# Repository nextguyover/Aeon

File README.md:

# Aeon

Aeon is a solar-powered colour e-ink photo frame designed around the [7.3inch Spectra 6](https://www.waveshare.com/7.3inch-e-paper-hat-e.htm) e-ink display. Powered using energy harvesting, Aeon achieves indefinite operation when placed in a bright indoor environment.

This repository contains the following design files for Aeon. 

- [Firmware](firmware)
- [Image Conversion Script](image_conversion)
- [Schematic and PCB Design](schematic_and_PCB)

See the the [blogpost](https://insertnewline.com/blog/aeon/) for a full write-up and additional file downloads.

Current Aeon version is v2.0, available on the [main branch](https://github.com/nextguyover/Aeon/tree/main). See older versions below:
- [v1.4](https://github.com/nextguyover/Aeon/tree/v1.4) - Using discontinued [7.3inch ACeP](https://www.waveshare.com/7.3inch-e-paper-hat-f.htm) e-ink display

## Firmware

The `/firmware` directory contains the firmware for the STM32 microcontroller.

### Flashing

Before flashing the firmware, the option bytes of the STM32 must be set. Using STM32CubeProgrammer, uncheck nSWBOOT0. The option byte options should look like this:

Next, flashing the firmware can be done using the STM32CubeIDE. Your STLink programmer should be connected to the programming pins on the PCB.

### Debugging

The firmware includes several debugging features. 

Any `printf` statements will be outputted to SWO, which can be read using STLink. Additionally, if debug mode is active, any logged data will be stored in an array, and written to the SD card just before going back to sleep. This debug mode is enabled by pressing and **holding** the refresh button to wake the device. The status LED will **flash rapidly** to indicate debug mode is active. Alternatively, the `DEBUG_MODE_FORCE_EN` flag in `main.h` forces debug mode to be enabled. This should be disabled during normal operation to prevent excessive SD card writes.

The `BATT_LOGGING` flag in logs to `/logfiles/batt-charge.csv` on the SD card. This only appends a new line to the file on each wake cycle, so it is safe to leave on for extended periods of time.

### ADC Calibration

The ADC for the battery voltage measurement should be calibrated as the accuracy of different STM32 chips can vary. The calibration process must be done manually by changing [this](/firmware/Core/Src/aeon.c#L108) value in the `aeon.c` file.

## Image Conversion

The `/image_conversion` folder contains a Python script to convert images to the SLIC format, which is the image format Aeon supports. 

### Preparation

Compile the photos you wish to display on Aeon, and save them in a directory. `.jpg`, `.png` and `.heic` files are supported. All images should be the same orientation. If a portrait orientation is chosen, rotate all portrait images 90 degrees clockwise. 

### Usage Instructions

The first step is preparing the SLIC conversion executable.

1. Git clone the SLIC repository `git clone https://github.com/bitbank2/SLIC.git`
2. Change directory `cd SLIC/linux/c_demo/`
3. Compile executable with `make`
4. Copy the executable to the `/image_conversion` directory

Next, install the required Python packages with `pip install -r requirements.txt`.

To convert a directory of images, run `python convert.py <input_dir>` where `<input_dir>` is the directory containing the images to convert. The converted images will be saved in a new directory named `img_out`.

Format the SD card in FAT32. The generated `.slc` files can then be copied to the `/images` directory of the SD card. *Do not rename the generated files.*

## Schematic and PCB Design

The `/schematic_and_PCB` directory contains the KiCad schematic and PCB design files for Aeon.

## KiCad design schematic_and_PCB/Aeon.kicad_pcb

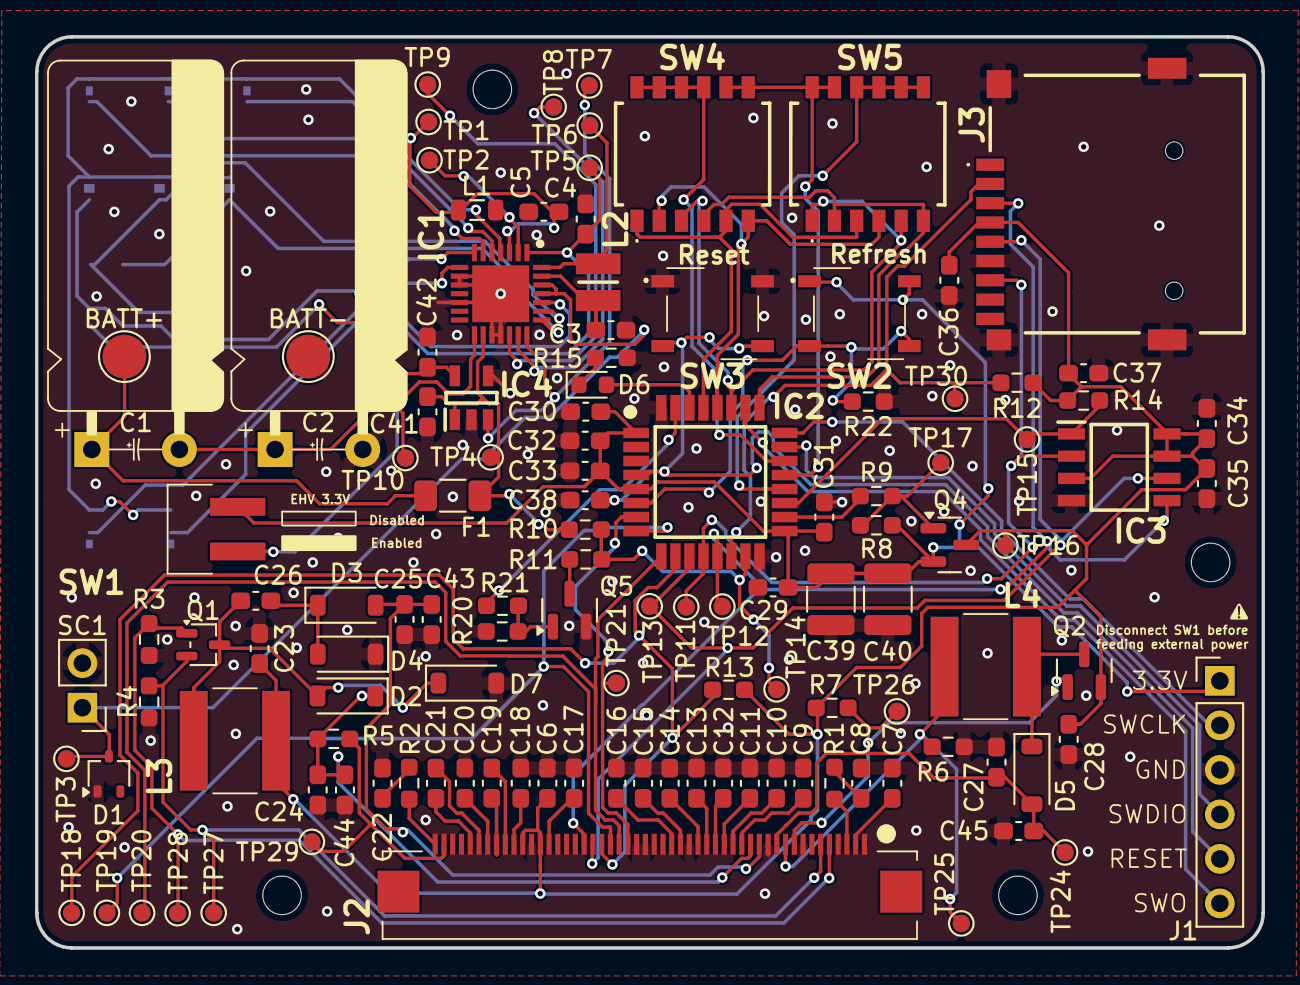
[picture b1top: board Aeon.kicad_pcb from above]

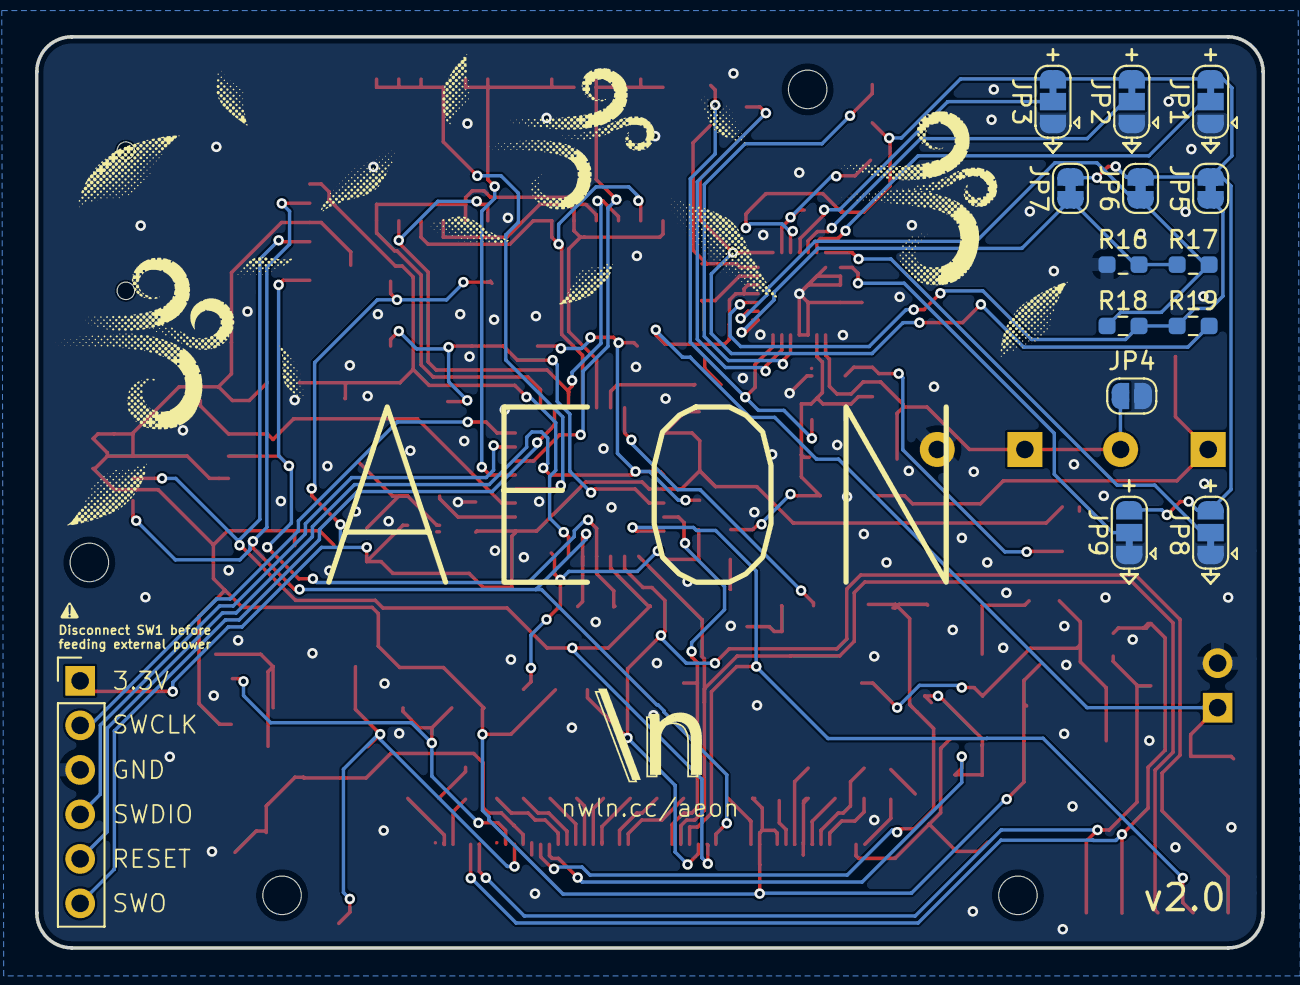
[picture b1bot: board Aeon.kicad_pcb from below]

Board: 2 copper layers, 70.0 x 52.0 mm, 135 parts (13 on the bottom side), 84 nets.

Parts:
BATT+: TestPoint_Pad_D2.5mm
BATT-: TestPoint_Pad_D2.5mm
C1, C2: 6F 2.7V; SUPERCAP
C3, C5: 10uF; C_0603_1608Metric_Pad1.08x0.95mm_HandSolder
C4: 22uF; C_0603_1608Metric_Pad1.08x0.95mm_HandSolder
C6, C43, C44, C45: 100nF/50V; C_0603_1608Metric_Pad1.08x0.95mm_HandSolder
C7, C22, C23: 4.7uF/25V; C_0603_1608Metric_Pad1.08x0.95mm_HandSolder
C8: 0.47uF/25V; C_0603_1608Metric_Pad1.08x0.95mm_HandSolder
C9, C10, C11, C12, C13, C14, C24, C25, C26, C27: 10uF/25V; C_0603_1608Metric_Pad1.08x0.95mm_HandSolder
C15, C16, C18, C19, C20, C21: 1uF/50V; C_0603_1608Metric_Pad1.08x0.95mm_HandSolder
C17: 2.2uF/6.3V; C_0603_1608Metric_Pad1.08x0.95mm_HandSolder
C28, C29: 4.7uF/10V; C_0603_1608Metric_Pad1.08x0.95mm_HandSolder
C30, C31, C35, C36: 100nF/10V; C_0603_1608Metric_Pad1.08x0.95mm_HandSolder
C32: 10nF/10V; C_0603_1608Metric_Pad1.08x0.95mm_HandSolder
C33: 1uF/10V; C_0603_1608Metric_Pad1.08x0.95mm_HandSolder
C34, C37: 10uF/10V; C_0603_1608Metric_Pad1.08x0.95mm_HandSolder
C38: 0.1uF/10V; C_0603_1608Metric_Pad1.08x0.95mm_HandSolder
C39, C40: 100uF/10V; C_1210_3225Metric
C41, C42: 1uF; C_0603_1608Metric_Pad1.08x0.95mm_HandSolder
D1: Zener_5V; SOT-323_SC-70
D2, D3, D4, D5: MBR0530; D_SOD-123
D6: DEBUG_LED; LED_0603_1608Metric
D7: BZT52C27; D_SOD-123
F1: 750mA Polyfuse; R_1206_3216Metric_Pad1.30x1.75mm_HandSolder
IC1: AEM10941-QFN; QFN50P500X500X90-29N-D
IC2: STM32L412K8T6; QFP80P900X900X160-32N
IC3: FM25L04B-GTR; SOIC127P602X173-8N
IC4: TPS7A0233PDBVR; SOT95P280X145-5N
J1: Conn_01x06_Pin; PinHeader_1x06_P2.54mm_Vertical
J2: FH34SRJ-50S-0.5SH50 - Colour E-Paper; FPC_CONN_2
J3: Micro_SD_Card; MICROSDCARD
JP1, JP2, JP3: SolderJumper_3_Open; SolderJumper-3_P1.3mm_Bridged2Bar23_RoundedPad1.0x1.5mm
JP4: SolderJumper_2_Open; SolderJumper-2_P1.3mm_Open_RoundedPad1.0x1.5mm
JP5, JP6, JP7: SolderJumper_2_Open; SolderJumper-2_P1.3mm_Bridged_RoundedPad1.0x1.5mm
JP8, JP9: SolderJumper_3_Open; SolderJumper-3_P1.3mm_Bridged2Bar12_RoundedPad1.0x1.5mm
L1: 10uH/50mA; L_0805_2012Metric
L2: 22uH/115mA; INDC2424X100N
L3, L4: 10uH/1A; NR6012T100ME_INDUCTOR_6012
Q1: SI1308EDL; SOT-323_SC-70
Q2, Q4: SI2301CDS-T1-E3; SOT-23
Q5: BSS138; SOT-23
R1, R2, R5: 0R; R_0603_1608Metric_Pad0.98x0.95mm_HandSolder
R3, R7, R8, R20: 1M; R_0603_1608Metric_Pad0.98x0.95mm_HandSolder
R4, R6: 0.2R; R_0603_1608Metric_Pad0.98x0.95mm_HandSolder
R9, R10, R21: 4.7K; R_0603_1608Metric_Pad0.98x0.95mm_HandSolder
R11, R12, R13, R14, R22: 10K; R_0603_1608Metric_Pad0.98x0.95mm_HandSolder
R15: 1K; R_0603_1608Metric_Pad0.98x0.95mm_HandSolder
R16, R17, R18, R19: X; R_0603_1608Metric_Pad0.98x0.95mm_HandSolder
SC1: EHV_SRC_Cell; PinHeader_1x02_P2.54mm_Vertical
SW1: SW_EHV_EN; SMD_2x_PIN_HEADER
SW2: REFRESH_BTN; PTS526SMG15JSMTR2LFS
SW3: RESET_BTN; PTS526SMG15JSMTR2LFS
SW4, SW5: SW_DIP_x06_SMD_1.27; 2186LPSRF
TP1, TP2, TP3, TP4, TP5, TP6, TP7, TP8, TP9, TP10, TP11, TP12, TP13, TP14, TP15, TP16, TP17, TP18, TP19, TP20, TP21, TP24, TP25, TP26, TP27, TP28, TP29, TP30: TestPoint_Pad_D1.0mm

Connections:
+3.3V: C29.2, C30.2, C31.2, C32.1, C33.2, C39.2, C40.2, IC2.1 (VDD_1), IC2.5 (VDDA/VREF+), IC2.17 (VDD_2), J1.1, Q4.2 (S), R8.1, SW1.2, SW2.1
+3.3V AUX: C6.2, C23.2, C28.2, C34.1, C35.2, C36.1, C37.2, IC3.3 (~WP), IC3.7 (~HOLD), IC3.8 (VDD), J2.38 (VDD), J2.40 (VDDIO), J3.4 (VDD), L3.1, Q2.2 (S), Q4.3 (D), R7.2, R12.1, R13.1, R14.1, TP16.1
AUX_PWR_EN: IC2.18 (PA8), R9.1
BATT_VDIV_EN: IC2.31 (PH3-BOOT0), R21.1
DISP_BUSY: IC2.9 (PA3), J2.29 (BUSY_N), TP20.1
DISP_CS: IC2.10 (PA4), J2.31 (CS#), R13.2, TP18.1
DISP_D/C: IC2.8 (PA2), J2.30 (D/C#), TP19.1
DISP_GDRC: J2.9 (GDRC), Q2.1 (G), R7.1, TP26.1
DISP_GDRH: J2.5 (GDRH), Q1.1 (G), R3.2, TP28.1
DISP_MOSI: IC2.13 (PA7), IC3.5 (SI), J2.33 (SIO), J3.3 (CMD), TP12.1
DISP_RESEC: J2.10 (RESEC), L4.1, R6.2, TP25.1
DISP_RESEH: J2.6 (RESEH), Q1.2 (S), R4.2, TP27.1
DISP_RST: IC2.7 (PA1), J2.28 (RES#), TP21.1
DISP_SCLK: IC2.11 (PA5), IC3.6 (SCK), J2.32 (SCL), J3.5 (CLK), TP13.1
DISP_VGH: J2.49 (VGH), R5.2, TP29.1
DISP_VGL: C25.2, C43.2, D3.2 (A), J2.13 (VGL)
DISP_VPC: C27.2, C45.2, D5.2 (A), J2.11 (VPC), TP24.1
DISP_VPH: C24.2, C44.2, D2.1 (K), J2.14 (VPH), R5.1
EHV_BATT: C41.1, F1.1, IC1.16 (BATT), IC4.1 (IN), R10.1, TP4.1
EHV_BOOST: C4.2, IC1.1 (BOOST), R19.2, TP5.1
EHV_BUCK: C5.2, IC1.3 (BUCK), JP1.3 (B), JP2.3 (B), JP3.3 (B), JP5.2 (B), JP6.2 (B), JP7.2 (B), JP8.3 (B), JP9.3 (B), L1.1, TP1.1
EHV_LDO_EN: IC1.21 (STATUS[0]), IC4.3 (EN), TP7.1
EHV_SRC: D1.3 (K), IC1.25 (SRC), IC1.26 (SRC), SC1.1 (+), TP3.1
EHV_SWBOOST: IC1.28 (SWBOOST), L2.1, TP6.1
EHV_SWBUCK: IC1.2 (SWBUCK), L1.2, TP2.1
FRAM_CS: IC2.19 (PA9), IC3.1 (~CS), R14.2, TP15.1
FRAM_MISO: IC2.12 (PA6), IC3.2 (SO), J3.7 (DAT0), TP11.1
GND: BATT-.1, C2.2, C3.2, C4.1, C5.1, C6.1, C7.1, C8.1, C9.1, C10.1, C11.1, C12.1, C13.1, C14.1, C15.1, C16.1, C17.1, C18.1, C20.1, C22.1, C23.1, C24.1, C25.1, C27.1, C28.1, C29.1, C30.1, C31.1, C32.2, C33.1, C34.2, C35.1, C36.2, C37.1, C38.2, C39.1, C40.1, C41.2, C42.1, C43.1, C44.1, C45.1, D1.1 (A), D4.1 (K), D7.2 (A), IC1.9 (FB_PRIM_D), IC1.10 (FB_PRIM_U), IC1.12 (ENHV), IC1.17 (PRIM), IC1.18 (ENLV), IC1.29 (PAD_(GND)), IC2.16 (VSS_1), IC2.32 (VSS_2), IC3.4 (VSS), IC4.2 (GND), IC4.4 (NC), J1.3, J2.8 (GND), J2.12 (GND), J2.21 (GNDA), J2.26 (BS0), J2.27 (BS1), J2.39 (GND), J3.6 (VSS), J3.9 (SHIELD), JP1.1 (A), JP2.1 (A), JP3.1 (A), JP4.1 (A), JP8.1 (A), JP9.1 (A), Q5.2 (S), R3.1, R4.1, R6.1, R15.2, R16.1, R20.2, R22.1, SC1.2 (-), SW3.1
unnamed: BATT+.1, C1.1, F1.2
unnamed: C8.2, R1.1
unnamed: C22.2, R2.1
unnamed: C26.2, D2.2 (A), D7.1 (K), L3.2, Q1.3 (D)
unnamed: C26.1, D3.1 (K), D4.2 (A)
unnamed: D5.1 (K), L4.2, Q2.3 (D)
unnamed: D6.2 (A), IC2.30 (PB7)
unnamed: D6.1 (K), R15.1
unnamed: C1.2, C2.1, IC1.15 (BAL), JP4.2 (B), TP10.1
unnamed: C3.1, IC1.27 (BUFSRC), L2.2
unnamed: IC1.6 (CFG[0]), JP1.2 (C)
unnamed: IC1.5 (CFG[1]), JP2.2 (C)
unnamed: IC1.4 (CFG[2]), JP3.2 (C)
unnamed: IC1.8 (SELMPP[0]), JP9.2 (C)
unnamed: IC1.7 (SELMPP[1]), JP8.2 (C)
unnamed: IC1.23 (SET_CHRDY), JP6.1 (A), R17.2, R18.1
unnamed: IC1.22 (SET_OVCH), JP7.1 (A), R16.2, R17.1
unnamed: IC1.24 (SET_OVDIS), JP5.1 (A), R18.2, R19.1
unnamed: IC1.20 (STATUS[1]), TP8.1
unnamed: IC1.19 (STATUS[2]), TP9.1
unnamed: IC2.6 (PA0-CK_IN), R22.2, SW2.2
unnamed: IC2.20 (PA10), SW5.7, SW5.8, SW5.9, SW5.10
unnamed: IC2.21 (PA11), SW4.7, SW4.8, SW5.11, SW5.12
unnamed: IC2.22 (PA12), SW4.9, SW4.10, SW4.11, SW4.12
unnamed: IC2.25 (PA15), SW4.4, SW5.2, SW5.6
unnamed: IC2.15 (PB1), R10.2, R11.1, TP14.1
unnamed: IC2.27 (PB4), SW4.3, SW5.1, SW5.5
unnamed: IC2.28 (PB5), SW4.2, SW4.6, SW5.4
unnamed: IC2.29 (PB6), SW4.1, SW4.5, SW5.3
unnamed: C42.2, IC4.5 (OUT), SW1.1
unnamed: C21.1, J2.45 (CP1N)
unnamed: C21.2, J2.46 (CP1P)
unnamed: C19.1, J2.42 (CP2N)
unnamed: C19.2, J2.43 (CP2P)
unnamed: J2.3 (FPL_VCOM), R1.2
unnamed: C15.2, J2.22 (REFN)
unnamed: C16.2, J2.23 (REFP)
unnamed: C7.2, J2.2 (TFT_VCOM)
unnamed: J2.50 (VCOMBD), R2.2
unnamed: C20.2, J2.44 (VCP1)
unnamed: C18.2, J2.41 (VCP2)
unnamed: C17.2, J2.37 (VDDDO)
unnamed: C9.2, J2.15 (VSH)
unnamed: C11.2, J2.17 (VSH_LV2)
unnamed: C10.2, J2.16 (VSH_LV)
unnamed: C12.2, J2.18 (VSL)
unnamed: C14.2, J2.20 (VSL_LV2)
unnamed: C13.2, J2.19 (VSL_LV)
unnamed: Q4.1 (G), R8.2, R9.2, TP17.1
unnamed: Q5.3 (D), R11.2
unnamed: Q5.1 (G), R20.1, R21.2
SD_CS: IC2.14 (PB0), J3.2 (DAT3/CD), R12.2, TP30.1
SOC_RST: C38.1, IC2.4 (NRST), J1.5, SW3.2
SOC_SWCLK: IC2.24 (PA14), J1.2
SOC_SWDIO: IC2.23 (PA13), J1.4
SOC_SWO: IC2.26 (PB3), J1.6

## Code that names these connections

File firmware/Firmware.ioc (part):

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Mcu.Name=STM32L412K8Tx
Mcu.Package=LQFP32
Mcu.UserName=STM32L412K8Tx
PA0-CK_IN.GPIOParameters=GPIO_PuPd,GPIO_Label
PA0-CK_IN.GPIO_Label=BTN IN
PA0-CK_IN.GPIO_PuPd=GPIO_NOPULL
PA0-CK_IN.Signal=GPIO_Input
PA1.GPIOParameters=GPIO_Label
PA1.GPIO_Label=DISP RST
PA1.Signal=GPIO_Output
PA10.GPIOParameters=GPIO_PuPd,GPIO_Label,GPIO_ModeDefaultOutputPP
PA10.GPIO_Label=SW OUT
PA10.GPIO_ModeDefaultOutputPP=GPIO_MODE_OUTPUT_OD
PA10.GPIO_PuPd=GPIO_NOPULL
PA10.Signal=GPIO_Output
PA11.GPIOParameters=GPIO_PuPd,GPIO_Label,GPIO_ModeDefaultOutputPP
PA11.GPIO_Label=SW OUT
PA11.GPIO_ModeDefaultOutputPP=GPIO_MODE_OUTPUT_OD
PA11.GPIO_PuPd=GPIO_NOPULL
PA11.Signal=GPIO_Output
PA12.GPIOParameters=GPIO_PuPd,GPIO_Label,GPIO_ModeDefaultOutputPP
PA12.GPIO_Label=SW OUT
PA12.GPIO_ModeDefaultOutputPP=GPIO_MODE_OUTPUT_OD
PA12.GPIO_PuPd=GPIO_NOPULL
PA12.Signal=GPIO_Output
PA13\ (JTMS/SWDIO).Mode=Trace_Asynchronous_SW
PA13\ (JTMS/SWDIO).Signal=SYS_JTMS-SWDIO
PA14\ (JTCK/SWCLK).Mode=Trace_Asynchronous_SW
PA14\ (JTCK/SWCLK).Signal=SYS_JTCK-SWCLK
PA15\ (JTDI).GPIOParameters=GPIO_PuPd,GPIO_Label
PA15\ (JTDI).GPIO_Label=SW IN
PA15\ (JTDI).GPIO_PuPd=GPIO_PULLUP
PA15\ (JTDI).Signal=GPIO_Input
PA2.GPIOParameters=GPIO_Speed,PinState,GPIO_Label
PA2.GPIO_Label=DISP DC
PA2.GPIO_Speed=GPIO_SPEED_FREQ_LOW
PA2.PinState=GPIO_PIN_RESET
PA2.Signal=GPIO_Output
PA3.GPIOParameters=GPIO_Label
PA3.GPIO_Label=DISP BUSY
PA3.Signal=GPIO_Input
PA4.GPIOParameters=GPIO_Speed,PinState,GPIO_Label
PA4.GPIO_Label=DISP CS
PA4.GPIO_Speed=GPIO_SPEED_FREQ_VERY_HIGH
PA4.PinState=GPIO_PIN_SET
PA4.Signal=GPIO_Output
PA5.Mode=Full_Duplex_Master
PA5.Signal=SPI1_SCK
PA6.Mode=Full_Duplex_Master
PA6.Signal=SPI1_MISO
PA7.Mode=Full_Duplex_Master
PA7.Signal=SPI1_MOSI
PA8.GPIOParameters=GPIO_Speed,PinState,GPIO_Label
PA8.GPIO_Label=AUX PWR EN
PA8.GPIO_Speed=GPIO_SPEED_FREQ_LOW
PA8.PinState=GPIO_PIN_SET
PA8.Signal=GPIO_Output
PA9.GPIOParameters=GPIO_Speed,PinState,GPIO_Label
PA9.GPIO_Label=FRAM_CS
PA9.GPIO_Speed=GPIO_SPEED_FREQ_VERY_HIGH
PA9.PinState=GPIO_PIN_SET
PA9.Signal=GPIO_Output
PB0.GPIOParameters=GPIO_Speed,PinState,GPIO_Label
PB0.GPIO_Label=SD_CS
PB0.GPIO_Speed=GPIO_SPEED_FREQ_VERY_HIGH
PB0.PinState=GPIO_PIN_SET
PB0.Signal=GPIO_Output
PB1.Signal=ADCx_IN16
PB3\ (JTDO/TRACESWO).Mode=Trace_Asynchronous_SW
PB3\ (JTDO/TRACESWO).Signal=SYS_JTDO-SWO
PB4\ (NJTRST).GPIOParameters=GPIO_PuPd,GPIO_Label
PB4\ (NJTRST).GPIO_Label=SW IN
PB4\ (NJTRST).GPIO_PuPd=GPIO_PULLUP
PB4\ (NJTRST).Signal=GPIO_Input
PB5.GPIOParameters=GPIO_PuPd,GPIO_Label
PB5.GPIO_Label=SW IN
PB5.GPIO_PuPd=GPIO_PULLUP
PB5.Signal=GPIO_Input
PB6.GPIOParameters=GPIO_PuPd,GPIO_Label
PB6.GPIO_Label=SW IN
PB6.GPIO_PuPd=GPIO_PULLUP
PB6.Signal=GPIO_Input
PB7.GPIOParameters=GPIO_Label
PB7.GPIO_Label=DEBUG_LED
PB7.Signal=GPIO_Output
PH3-BOOT0\ (BOOT0).GPIOParameters=GPIO_Label
PH3-BOOT0\ (BOOT0).GPIO_Label=BATT_VDIV_EN
PH3-BOOT0\ (BOOT0).Signal=GPIO_Output
RCC.HSE_VALUE=8000000
RCC.SYSCLKFreq_VALUE=80000000
RCC.SYSCLKSource=RCC_SYSCLKSOURCE_PLLCLK
board=custom

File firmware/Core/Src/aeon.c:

#include "aeon.h"

#include <stdio.h>

#include "fram.h"
#include "main.h"
#include "sd.h"
#include "stm32l4xx_hal.h"

const char *wake_reason_t_str[] = {"WAKE_REASON_RESET",
                                   "WAKE_REASON_STBY_REFRESH_BTN",
                                   "WAKE_REASON_STBY_RTC"};

const char *sleep_reason_t_str[] = {"SLEEP_REASON_NULL",
                                    "SLEEP_REASON_FIRST_AFTER_REFRESH",
                                    "SLEEP_REASON_NORM_ITER",
                                    "SLEEP_REASON_LOW_BATT",
                                    "SLEEP_REASON_NO_IMAGE",
                                    "SLEEP_REASON_NO_SD",
                                    "SLEEP_REASON_REFRESH_DISABLED"};

/**
 * @brief Select the SPI device to communicate with.
 *
 * @param spi_device SPI device to select
 */
void spi_device_select(enum spi_device_t spi_device) {
    HAL_GPIO_WritePin(SD_CS_GPIO_Port, SD_CS_Pin,
                      spi_device == AEON_SPI_SD || spi_device == AEON_SPI_OFF
                          ? GPIO_PIN_RESET
                          : GPIO_PIN_SET);
    HAL_GPIO_WritePin(DISP_CS_GPIO_Port, DISP_CS_Pin,
                      spi_device == AEON_SPI_DISP || spi_device == AEON_SPI_OFF
                          ? GPIO_PIN_RESET
                          : GPIO_PIN_SET);
    HAL_GPIO_WritePin(FRAM_CS_GPIO_Port, FRAM_CS_Pin,
                      spi_device == AEON_SPI_FRAM || spi_device == AEON_SPI_OFF
                          ? GPIO_PIN_RESET
                          : GPIO_PIN_SET);
}

void set_aux_pwr(bool enable) {
    HAL_GPIO_WritePin(AUX_PWR_EN_GPIO_Port, AUX_PWR_EN_Pin,
                      enable ? GPIO_PIN_SET : GPIO_PIN_RESET);
}

/**
 * PA12, PA11, PA10 should be set to 1 one at at time.
 *
 * PB6, PB5, PB4, PA15 are read each time that one of the above are enabled.
 *
 * When PA12 is enabled, PB6, PB5, PB4, PA15 values correspond to the bits 11,
 * 10, 9, 8 of the toggle switch. When PA11 is enabled, PB6, PB5, PB4, PA15
 * values correspond to the bits 7, 6, 5, 4 of the toggle switch. When PA10 is
 * enabled, PB6, PB5, PB4, PA15 values correspond to the bits 3, 2, 1, 0 of the
 * toggle switch.
 */
uint16_t get_toggle_sw_bits() {
    uint16_t bits = 0;

    HAL_GPIO_WritePin(GPIOA, GPIO_PIN_12, GPIO_PIN_RESET);
    HAL_GPIO_WritePin(GPIOA, GPIO_PIN_11, GPIO_PIN_SET);
    HAL_GPIO_WritePin(GPIOA, GPIO_PIN_10, GPIO_PIN_SET);
    HAL_Delay(1);

    bits |= HAL_GPIO_ReadPin(GPIOB, GPIO_PIN_6) << 11;
    bits |= HAL_GPIO_ReadPin(GPIOB, GPIO_PIN_5) << 10;
    bits |= HAL_GPIO_ReadPin(GPIOB, GPIO_PIN_4) << 9;
    bits |= HAL_GPIO_ReadPin(GPIOA, GPIO_PIN_15) << 8;

    HAL_GPIO_WritePin(GPIOA, GPIO_PIN_12, GPIO_PIN_SET);
    HAL_GPIO_WritePin(GPIOA, GPIO_PIN_11, GPIO_PIN_RESET);
    HAL_GPIO_WritePin(GPIOA, GPIO_PIN_10, GPIO_PIN_SET);
    HAL_Delay(1);

    bits |= HAL_GPIO_ReadPin(GPIOB, GPIO_PIN_6) << 7;
    bits |= HAL_GPIO_ReadPin(GPIOB, GPIO_PIN_5) << 6;
    bits |= HAL_GPIO_ReadPin(GPIOB, GPIO_PIN_4) << 5;
    bits |= HAL_GPIO_ReadPin(GPIOA, GPIO_PIN_15) << 4;

    HAL_GPIO_WritePin(GPIOA, GPIO_PIN_12, GPIO_PIN_SET);
    HAL_GPIO_WritePin(GPIOA, GPIO_PIN_11, GPIO_PIN_SET);
    HAL_GPIO_WritePin(GPIOA, GPIO_PIN_10, GPIO_PIN_RESET);
    HAL_Delay(1);

    bits |= HAL_GPIO_ReadPin(GPIOB, GPIO_PIN_6) << 3;
    bits |= HAL_GPIO_ReadPin(GPIOB, GPIO_PIN_5) << 2;
    bits |= HAL_GPIO_ReadPin(GPIOB, GPIO_PIN_4) << 1;
    bits |= HAL_GPIO_ReadPin(GPIOA, GPIO_PIN_15) << 0;

    bits = (~bits) & 0x0FFF;

    return bits;
}

/**
 * Enable VDIV switch and read the battery voltage with the ADC.
 */
bool batt_threshold_check(double *batt_voltage_out) {
    HAL_GPIO_WritePin(BATT_VDIV_EN_GPIO_Port, BATT_VDIV_EN_Pin, GPIO_PIN_SET);
    HAL_Delay(10);

    HAL_ADC_Start(&hadc1);
    HAL_ADC_PollForConversion(&hadc1, 100);
    uint32_t adcValue = HAL_ADC_GetValue(&hadc1);
    double batt_voltage = (double)adcValue / 4095.0 *
                          6.14;  // this value has to be manually calibrated
    HAL_ADC_Stop(&hadc1);

    HAL_GPIO_WritePin(BATT_VDIV_EN_GPIO_Port, BATT_VDIV_EN_Pin, GPIO_PIN_RESET);

    if (batt_voltage_out != NULL) {
        *batt_voltage_out = batt_voltage;
    }

    return batt_voltage > BATT_THRESHOLD;
}

bool check_debug_mode_en() {
    if (GET_BTN_IN() == GPIO_PIN_SET) {
        SET_DEBUG_LED(true);
        HAL_Delay(1000);
        if (GET_BTN_IN() == GPIO_PIN_SET) {
            for (int i = 0; i < 10; i++) {
                SET_DEBUG_LED(true);
                HAL_Delay(50);
                SET_DEBUG_LED(false);
                HAL_Delay(50);
            }
            printf("Debug mode enabled due to button press!\n");
            return true;
        }
        SET_DEBUG_LED(false);
    }
    return false;
}

uint32_t calculate_update_sleep_duration(uint32_t remaining_duration,
                                         uint16_t current_interval_sw_value) {
    uint32_t new_duration;

    // if remaining duration is not 0, sleep for the remaining duration or the
    // default duration, whichever is smaller
    if (remaining_duration != 0) {
        if (remaining_duration > SLEEP_DURATION_DEFAULT) {
            fram_set_sleep_duration(remaining_duration -
                                    SLEEP_DURATION_DEFAULT);
            new_duration = SLEEP_DURATION_DEFAULT;
        } else {
            fram_set_sleep_duration(0);
            new_duration = remaining_duration;
        }
        return new_duration;
    }

    // else, calculate sleep duration based on the interval switch value
    // convert toggle switch value directly to hours (TODO: consider changing
    // this)
    current_interval_sw_value =
        current_interval_sw_value == 0
            ? 24
            : current_interval_sw_value;  // if 0, set to 24 hours
    new_duration =
        current_interval_sw_value * 60 * 60;  // convert hours to seconds
    if (new_duration > SLEEP_DURATION_DEFAULT) {
        fram_set_sleep_duration(new_duration - SLEEP_DURATION_DEFAULT);
        new_duration = SLEEP_DURATION_DEFAULT;
    } else {
        fram_set_sleep_duration(0);
    }
    return new_duration;
}

/**
 * Enter sleep mode.
 */
void enter_sleep(int sleep_seconds) {
    if (DBG) {
        printf("Sleeping for %d seconds...\n", sleep_seconds);
    }

    spi_device_select(AEON_SPI_SD);
    if (BATT_LOGGING)
        sd_append_batt_charge_log(sleep_seconds);  // append battery charge log
                                                   // to SD card
    if (runtime_debug_mode || DEBUG_MODE_FORCE_EN)
        sd_write_logfile();  // write debug log to SD card
    sd_close();              // unmount SD card

    fram_set_unsafe_shutdown(false);  // clear unsafe shutdown flag

    SET_AUX_PWR(false);               // disable AUX PWR
    spi_device_select(AEON_SPI_OFF);  // disable all CS lines to prevent
                                      // powering AUX via CS pull-up resistors

    HAL_RTCEx_SetWakeUpTimer_IT(&hrtc, sleep_seconds,
                                RTC_WAKEUPCLOCK_CK_SPRE_16BITS,
                                0);  // set wake up time

    // HAL_PWREx_EnablePullUpPullDownConfig(); // enable pull-ups
    // enabling internal pullups actually uses about 0.5uA more current, so not
    // using it

    // HAL_PWREx_EnableGPIOPullUp(AUX_PWR_EN_GPIO_Port, AUX_PWR_EN_Pin); //
    // enable pull-up on AUX PWR EN pin

    // Disable wake-up pin first to clear any pending wake-up event
    HAL_PWR_DisableWakeUpPin(PWR_WAKEUP_PIN1);
    
    // Clear all wake-up flags before enabling wake-up pin
    // This prevents immediate re-wake if button is still pressed
    __HAL_PWR_CLEAR_FLAG(PWR_FLAG_WU);
    
    HAL_PWR_EnableWakeUpPin(PWR_WAKEUP_PIN1_HIGH);

    HAL_PWR_EnterSTANDBYMode();  // go to low power standby mode

    printf("Should not reach here, something has gone wrong...\n");

    while (true) {
        SET_DEBUG_LED(true);
        HAL_Delay(200);
        SET_DEBUG_LED(false);
        HAL_Delay(200);

        HAL_PWR_EnterSTANDBYMode();
    }
}

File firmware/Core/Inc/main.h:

/* USER CODE BEGIN Header */
/**
 ******************************************************************************
 * @file           : main.h
 * @brief          : Header for main.c file.
 *                   This file contains the common defines of the application.
 ******************************************************************************
 * @attention
 *
 * Copyright (c) 2024 STMicroelectronics.
 * All rights reserved.
 *
 * This software is licensed under terms that can be found in the LICENSE file
 * in the root directory of this software component.
 * If no LICENSE file comes with this software, it is provided AS-IS.
 *
 ******************************************************************************
 */
/* USER CODE END Header */

/* Define to prevent recursive inclusion -------------------------------------*/
#ifndef __MAIN_H
#define __MAIN_H

#ifdef __cplusplus
extern "C" {
#endif

/* Includes ------------------------------------------------------------------*/
#include "stm32l4xx_hal.h"

/* Private includes ----------------------------------------------------------*/
/* USER CODE BEGIN Includes */
#include <stdbool.h>

#include "aeon.h"

/* USER CODE END Includes */

/* Exported types ------------------------------------------------------------*/
/* USER CODE BEGIN ET */

/* USER CODE END ET */

/* Exported constants --------------------------------------------------------*/
/* USER CODE BEGIN EC */

/* USER CODE END EC */

/* Exported macro ------------------------------------------------------------*/
/* USER CODE BEGIN EM */

/* USER CODE END EM */

/* Exported functions prototypes ---------------------------------------------*/
void Error_Handler(void);

/* USER CODE BEGIN EFP */

/* USER CODE END EFP */

/* Private defines -----------------------------------------------------------*/
#define BTN_IN_Pin GPIO_PIN_0
#define BTN_IN_GPIO_Port GPIOA
#define DISP_RST_Pin GPIO_PIN_1
#define DISP_RST_GPIO_Port GPIOA
#define DISP_DC_Pin GPIO_PIN_2
#define DISP_DC_GPIO_Port GPIOA
#define DISP_BUSY_Pin GPIO_PIN_3
#define DISP_BUSY_GPIO_Port GPIOA
#define DISP_CS_Pin GPIO_PIN_4
#define DISP_CS_GPIO_Port GPIOA
#define SD_CS_Pin GPIO_PIN_0
#define SD_CS_GPIO_Port GPIOB
#define AUX_PWR_EN_Pin GPIO_PIN_8
#define AUX_PWR_EN_GPIO_Port GPIOA
#define FRAM_CS_Pin GPIO_PIN_9
#define FRAM_CS_GPIO_Port GPIOA
#define SW_OUT_Pin GPIO_PIN_10
#define SW_OUT_GPIO_Port GPIOA
#define SW_OUTA11_Pin GPIO_PIN_11
#define SW_OUTA11_GPIO_Port GPIOA
#define SW_OUTA12_Pin GPIO_PIN_12
#define SW_OUTA12_GPIO_Port GPIOA
#define SW_IN_Pin GPIO_PIN_15
#define SW_IN_GPIO_Port GPIOA
#define SW_INB4_Pin GPIO_PIN_4
#define SW_INB4_GPIO_Port GPIOB
#define SW_INB5_Pin GPIO_PIN_5
#define SW_INB5_GPIO_Port GPIOB
#define SW_INB6_Pin GPIO_PIN_6
#define SW_INB6_GPIO_Port GPIOB
#define DEBUG_LED_Pin GPIO_PIN_7
#define DEBUG_LED_GPIO_Port GPIOB
#define BATT_VDIV_EN_Pin GPIO_PIN_3
#define BATT_VDIV_EN_GPIO_Port GPIOH

/* USER CODE BEGIN Private defines */
extern SPI_HandleTypeDef hspi1;
extern RTC_HandleTypeDef hrtc;
extern ADC_HandleTypeDef hadc1;
extern RNG_HandleTypeDef hrng;

#define SD_SPI_HANDLE hspi1

#define DBG_SWO_EN true  // enable SWO debug output
#define DEBUG_MODE_FORCE_EN \
    false  // force debug mode (should only be enabled for testing, as full logs
           // will be written to SD card)

#define STR(x) #x

#define DBG (DBG_SWO_EN || runtime_debug_mode)

#define DISABLE_BATT_THRESHOLD_CHECK \
    false  // set to true to disable functionality where device relies on ADC
           // battery measurement to return to sleep when battery is low

#define BATT_LOGGING true  // enable battery logging to SD card

#define SET_DEBUG_LED(x)                                  \
    HAL_GPIO_WritePin(DEBUG_LED_GPIO_Port, DEBUG_LED_Pin, \
                      (x) ? GPIO_PIN_SET : GPIO_PIN_RESET)
#define SET_AUX_PWR(x)                                      \
    HAL_GPIO_WritePin(AUX_PWR_EN_GPIO_Port, AUX_PWR_EN_Pin, \
                      (x) ? GPIO_PIN_RESET : GPIO_PIN_SET)

#define SET_DISP_CS(x)                                \
    HAL_GPIO_WritePin(DISP_CS_GPIO_Port, DISP_CS_Pin, \
                      (x) ? GPIO_PIN_SET : GPIO_PIN_RESET)
#define SET_DISP_DC(x)                                \
    HAL_GPIO_WritePin(DISP_DC_GPIO_Port, DISP_DC_Pin, \
                      (x) ? GPIO_PIN_SET : GPIO_PIN_RESET)
#define SET_DISP_RST(x)                                 \
    HAL_GPIO_WritePin(DISP_RST_GPIO_Port, DISP_RST_Pin, \
                      (x) ? GPIO_PIN_SET : GPIO_PIN_RESET)
#define GET_DISP_BUSY() HAL_GPIO_ReadPin(DISP_BUSY_GPIO_Port, DISP_BUSY_Pin)

#define GET_BTN_IN() HAL_GPIO_ReadPin(BTN_IN_GPIO_Port, BTN_IN_Pin)

extern enum wake_reason_t wake_reason;

extern bool runtime_debug_mode;  // when true, full log is written to SD card
                                 // is set true initially, will set false after
                                 // initialisation

extern uint32_t wake_cycle_count;

extern char debug_output_arr[20000];
extern int debug_output_arr_index;

extern uint32_t wake_cycle_count;
extern double batt_voltage;

/* USER CODE END Private defines */

#ifdef __cplusplus
}
#endif

#endif /* __MAIN_H */

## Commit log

2025-02-22 init
2025-12-12 rename output files more clearly, added img randomiser, fixed bugs
2025-12-21 reverted horizontal scaling
2025-12-21 finalised processing
2025-12-21 correctly interpreting and transferring pixel data
2025-12-27 double refresh issue fix
2025-12-27 Add battery threshold check functionality control
2025-12-27 moved definition
2026-03-15 Import symbol and footprint libs
2026-03-17 Change electrical design to match Spectra 6 driver reference
2026-03-23 Change colour palette for Spectra 6
2026-03-23 Improve image processing pipeline
2026-04-06 Add SD card info to readme
2026-04-06 Update schematic component values
